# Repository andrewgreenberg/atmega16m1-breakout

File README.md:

# atmega16m1-breakout
Breakout for the ATMega16M1 / ATMega32M1 / ATMega64M1 in the TQFP package.

Has 16 MHz crystal and CAN transceiver... because why else would you use the ATMega16m1?!

You can order it directly from OSH Park if you want, [here's the link](https://oshpark.com/shared_projects/IkiqLfbC).

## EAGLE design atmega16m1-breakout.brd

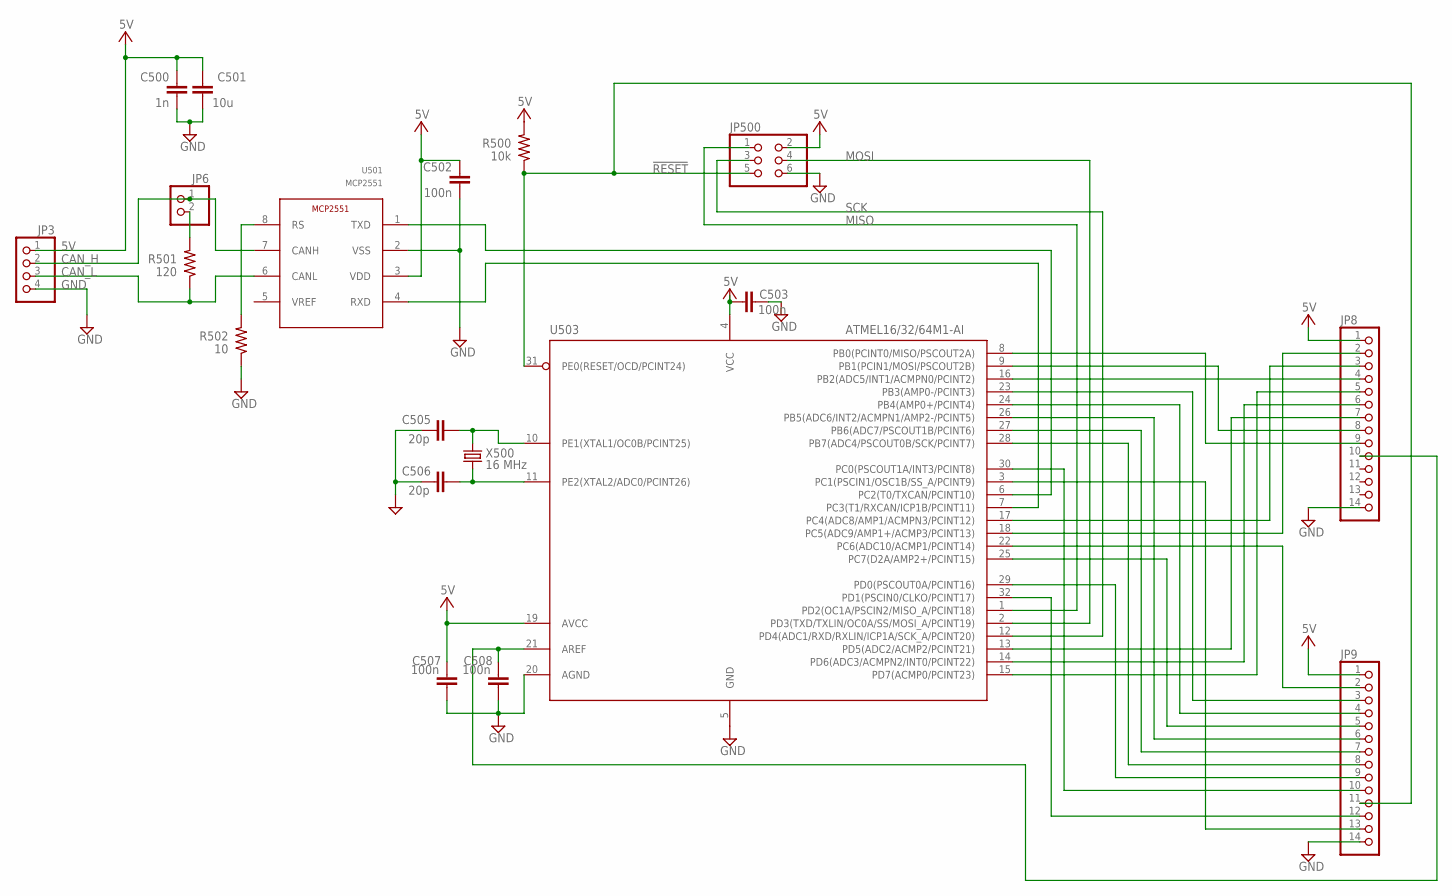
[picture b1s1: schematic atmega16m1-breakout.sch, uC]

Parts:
C500: 1n; 0603-B-NOSILK
C501: 10u; 0805-B-NOSILK
C502, C503, C507, C508: 100n; 0603-B-NOSILK
C505, C506: 20p; 0603-B-NOSILK
JP3: PINHD-1X4; 1X04
JP6: PINHD-1X2; 1X02
JP8, JP9: PINHD-1X14; 1X14
JP500: PINHD-2X3; 2X03
R500: 10k; 0603-B-NOSILK
R501: 120; 0603-B-NOSILK
R502: 10; 0603-B-NOSILK
U501: MCP2551; SO08
U503: ATMEL16/32/64M1-AI; TQFP32-08
X500: 16 MHz; ABM3

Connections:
5V: C500.1, C501.1, C502.1, C503.2, C507.1, JP3.1, JP8.1, JP9.1, JP500.2, R500.2, U501.3 (VDD), U503.4 (VCC), U503.19 (AVCC)
!RESET: JP9.11, JP500.5, R500.1, U503.31 (PE0(RESET/OCD/PCINT24))
AREF: C508.1, JP8.10, U503.21 (AREF)
CAN_H: JP3.2, JP6.1, U501.7 (CANH)
CAN_L: JP3.3, R501.1, U501.6 (CANL)
GND: C500.2, C501.2, C502.2, C503.1, C505.2, C506.2, C507.2, C508.2, JP3.4, JP8.14, JP9.14, JP500.6, R502.1, U501.2 (VSS), U503.5 (GND), U503.20 (AGND)
MISO: JP500.1, U503.1 (PD2(OC1A/PSCIN2/MISO_A/PCINT18))
MOSI: JP500.4, U503.2 (PD3(TXD/TXLIN/OC0A/SS/MOSI_A/PCINT19))
unnamed: JP6.2, R501.2
unnamed: R502.2, U501.8 (RS)
PB0: JP8.9, U503.8 (PB0(PCINT0/MISO/PSCOUT2A))
PB1: JP8.8, U503.9 (PB1(PCIN1/MOSI/PSCOUT2B))
PB2: JP8.4, U503.16 (PB2(ADC5/INT1/ACMPN0/PCINT2))
PB3: JP9.3, U503.23 (PB3(AMP0-/PCINT3))
PB4: JP9.4, U503.24 (PB4(AMP0+/PCINT4))
PB5: JP9.6, U503.26 (PB5(ADC6/INT2/ACMPN1/AMP2-/PCINT5))
PB6: JP9.7, U503.27 (PB6(ADC7/PSCOUT1B/PCINT6))
PB7: JP9.8, U503.28 (PB7(ADC4/PSCOUT0B/SCK/PCINT7))
PC0: JP9.10, U503.30 (PC0(PSCOUT1A/INT3/PCINT8))
PC1: JP9.13, U503.3 (PC1(PSCIN1/OSC1B/SS_A/PCINT9))
PC4: JP8.3, U503.17 (PC4(ADC8/AMP1/ACMPN3/PCINT12))
PC5: JP8.2, U503.18 (PC5(ADC9/AMP1+/ACMP3/PCINT13))
PC6: JP9.2, U503.22 (PC6(ADC10/ACMP1/PCINT14))
PC7: JP9.5, U503.25 (PC7(D2A/AMP2+/PCINT15))
PD0: JP9.9, U503.29 (PD0(PSCOUT0A/PCINT16))
PD1: JP9.12, U503.32 (PD1(PSCIN0/CLKO/PCINT17))
PD5: JP8.7, U503.13 (PD5(ADC2/ACMP2/PCINT21))
PD6: JP8.6, U503.14 (PD6(ADC3/ACMPN2/INT0/PCINT22))
PD7: JP8.5, U503.15 (PD7(ACMP0/PCINT23))
PE2: C506.1, U503.11 (PE2(XTAL2/ADC0/PCINT26)), X500.P1 (1)
PE3: C505.1, U503.10 (PE1(XTAL1/OC0B/PCINT25)), X500.P2 (2)
RXCAN: U501.4 (RXD), U503.7 (PC3(T1/RXCAN/ICP1B/PCINT11))
SCK: JP500.3, U503.12 (PD4(ADC1/RXD/RXLIN/ICP1A/SCK_A/PCINT20))
TXCAN: U501.1 (TXD), U503.6 (PC2(T0/TXCAN/PCINT10))

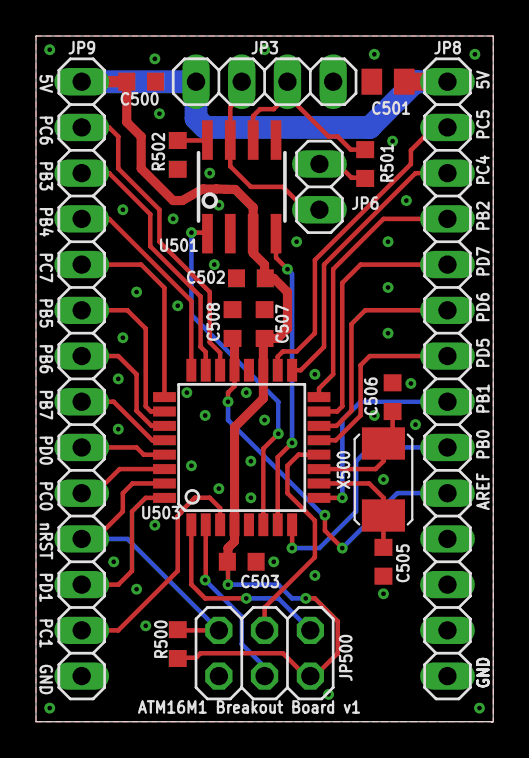
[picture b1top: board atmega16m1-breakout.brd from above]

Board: 2 copper layers, 25.4 x 38.1 mm, 19 parts (0 on the bottom side), 34 nets.

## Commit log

2017-10-14 Yep, it's a breakout.
2017-10-14 Oh yeah. BOM. And BOM cleanup.
2017-10-14 Link to OSH Park.
